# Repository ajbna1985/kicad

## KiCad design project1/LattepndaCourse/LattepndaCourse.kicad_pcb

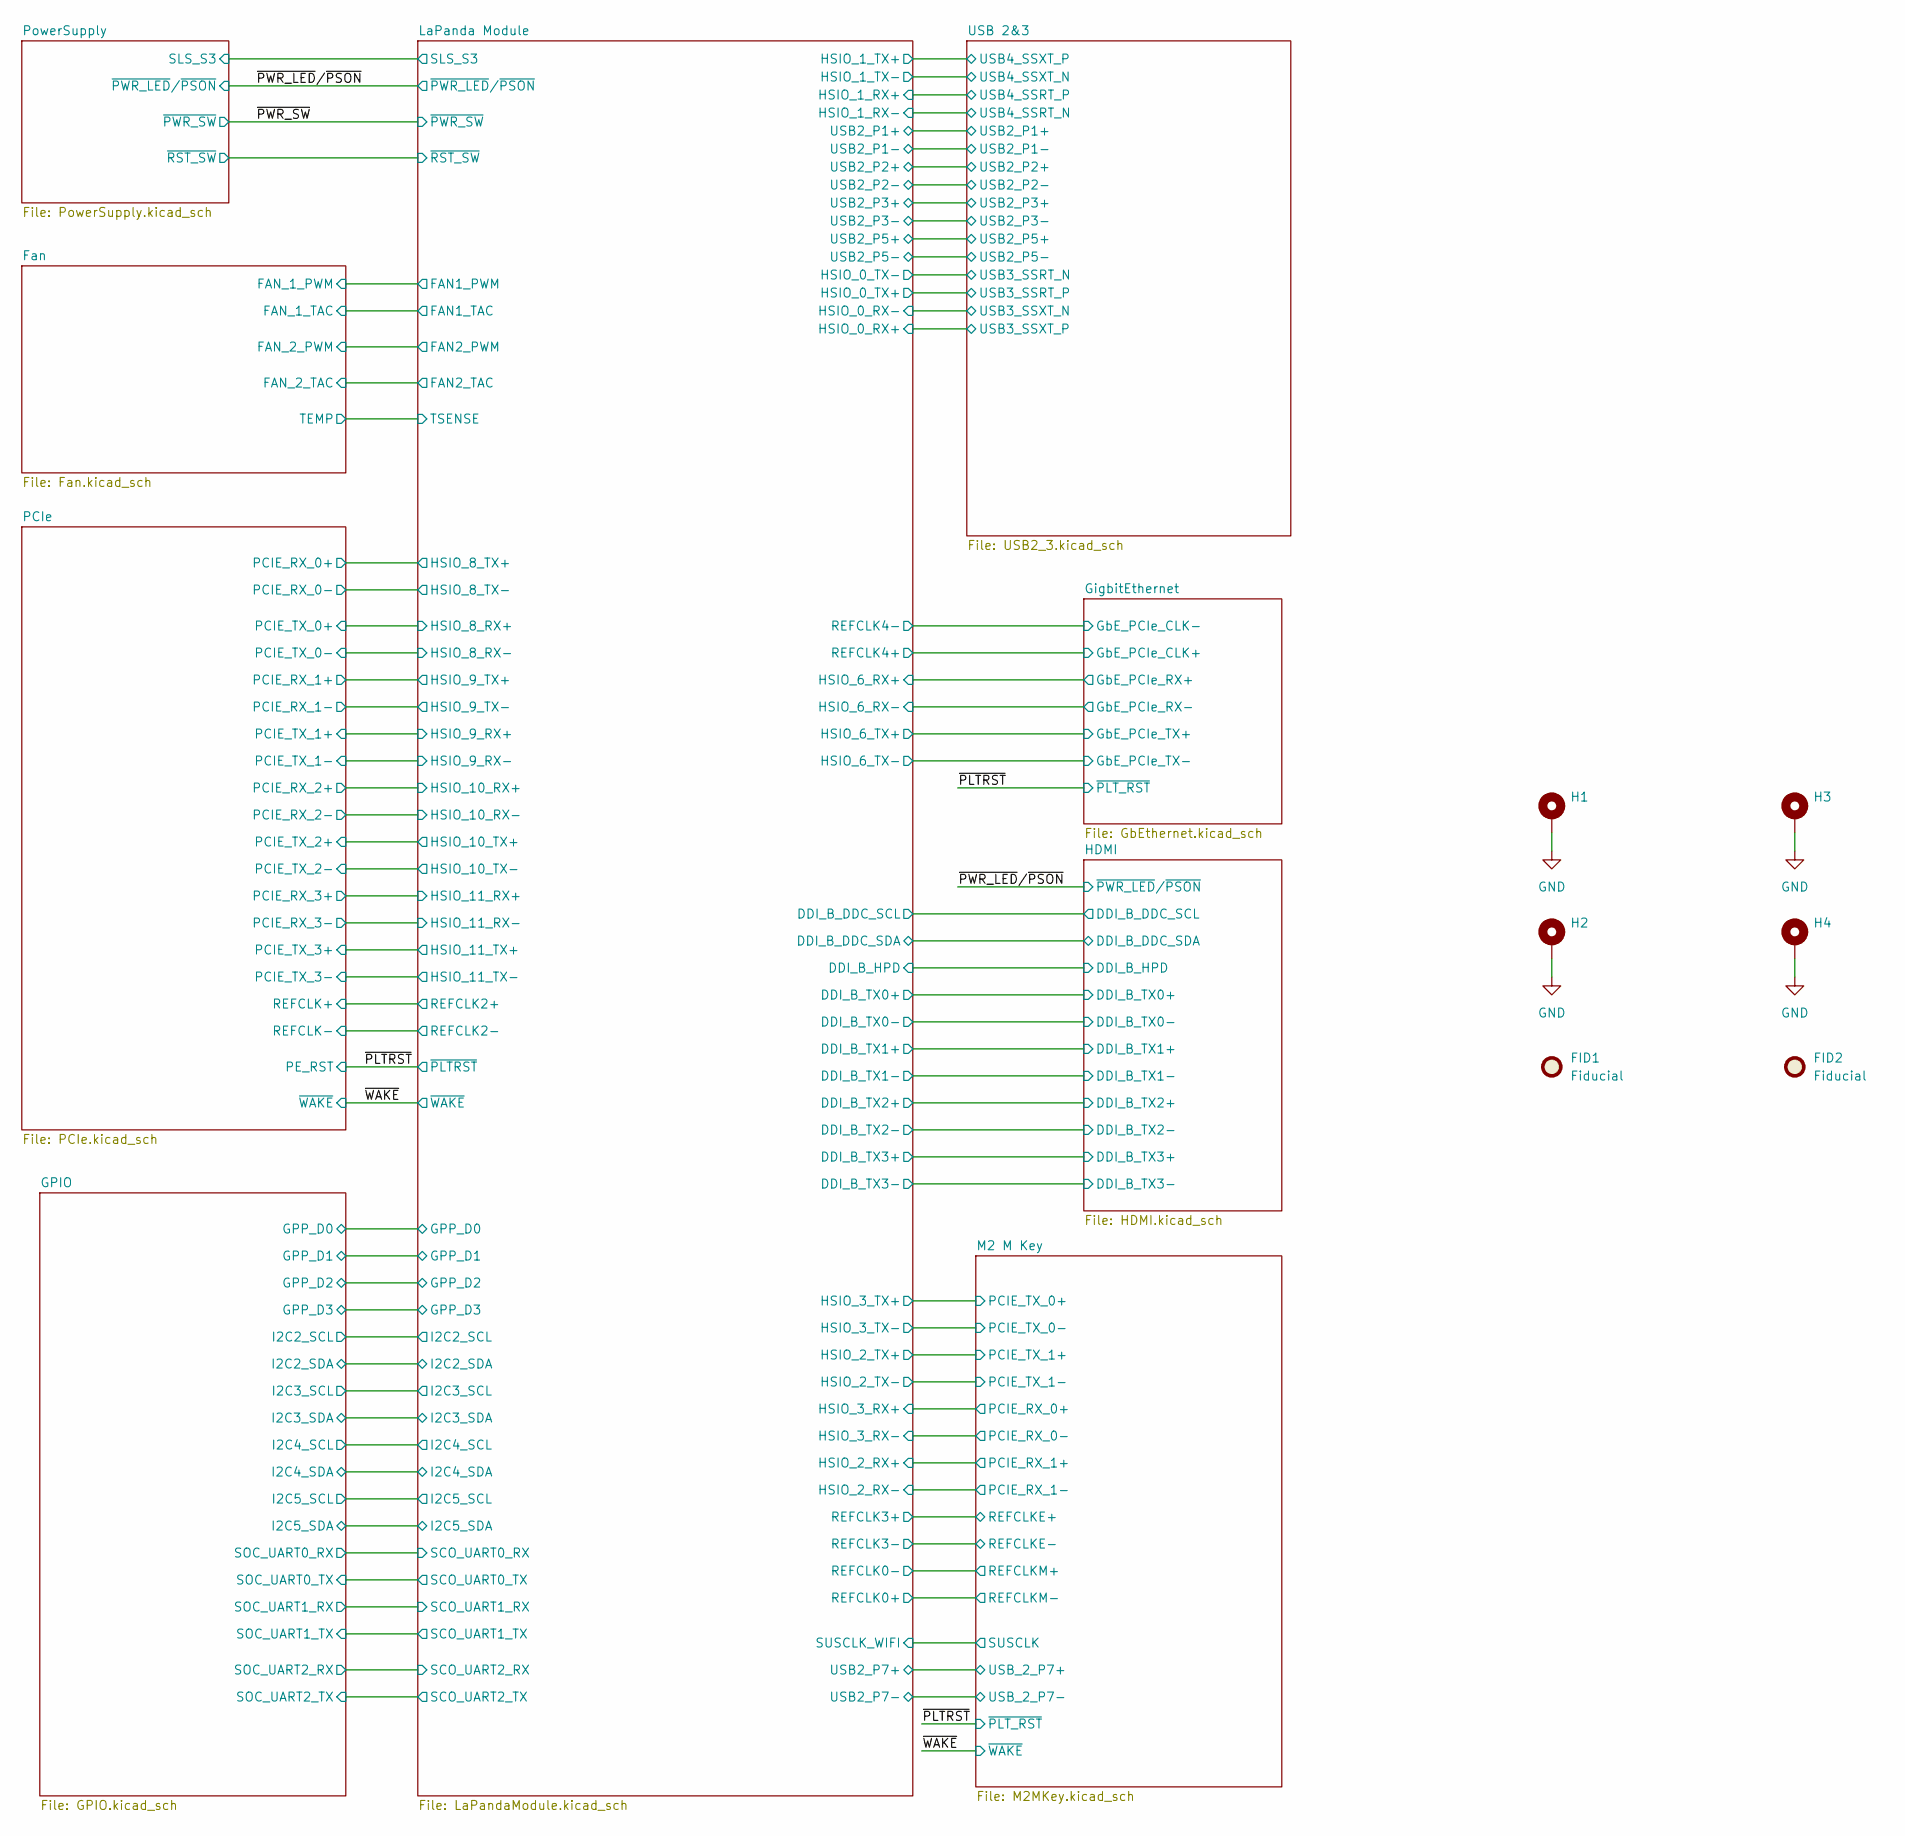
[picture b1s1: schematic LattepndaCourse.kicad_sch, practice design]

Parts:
FID1, FID2: Fiducial; Fiducial_0.5mm_Mask1mm
H1, H2, H3, H4: MountingHole_Pad; MountingHole_3.2mm_M3_Pad_Via

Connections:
+5V: H1.1 (1_1), H2.1 (1_1), H3.1 (1_1), H4.1 (1_1); also elsewhere on the board

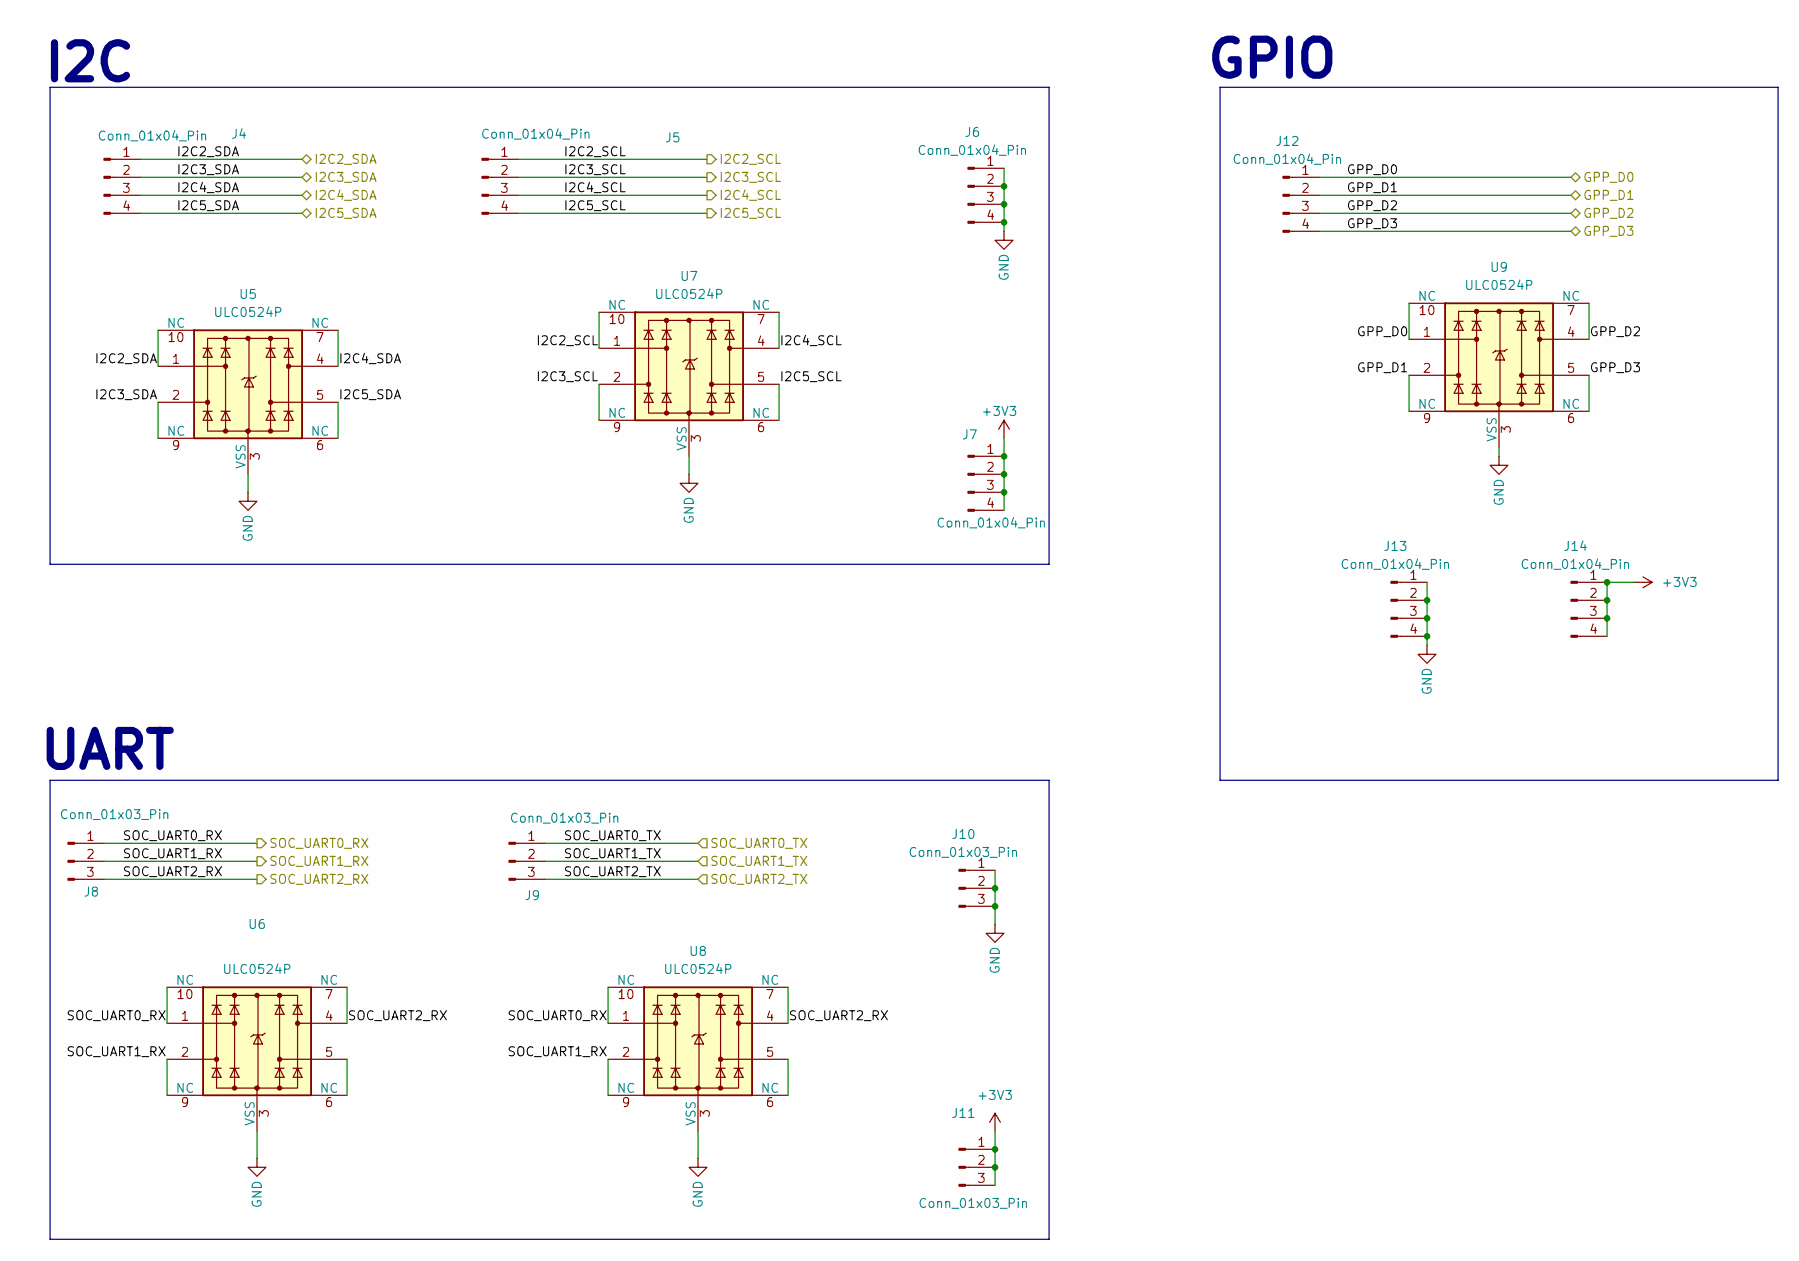
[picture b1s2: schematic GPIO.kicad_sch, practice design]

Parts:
J4, J5, J6, J7, J12, J13, J14: Conn_01x04_Pin; PinHeader_1x03_P2.54mm_Vertical
J8, J9, J10, J11: Conn_01x03_Pin; PinHeader_1x03_P2.54mm_Vertical
U5, U6, U7, U8, U9: ULC0524P; Diodes_UDFN-10_1.0x2.5mm_P0.5mm

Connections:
+3V3: J7.1, J7.2, J7.3, J7.4, J11.1, J11.2, J11.3, J14.1, J14.2, J14.3, J14.4; also elsewhere on the board
+5V: J6.1, J6.2, J6.3, J6.4, J10.1, J10.2, J10.3, J13.1, J13.2, J13.3, J13.4, U5.3 (VSS), U5.8 (VSS), U6.3 (VSS), U6.8 (VSS), U7.3 (VSS), U7.8 (VSS), U8.3 (VSS), U8.8 (VSS), U9.3 (VSS), U9.8 (VSS); also elsewhere on the board
/GPIO/GPP_D0: J12.1, U9.1, U9.10 (NC); also elsewhere on the board
/GPIO/GPP_D1: J12.2, U9.2, U9.9 (NC); also elsewhere on the board
/GPIO/GPP_D2: J12.3, U9.4, U9.7 (NC); also elsewhere on the board
/GPIO/GPP_D3: J12.4, U9.5, U9.6 (NC); also elsewhere on the board
/GPIO/I2C2_SCL: J5.1, U7.1, U7.10 (NC); also elsewhere on the board
/GPIO/I2C2_SDA: J4.1, U5.1, U5.10 (NC); also elsewhere on the board
/GPIO/I2C3_SCL: J5.2, U7.2, U7.9 (NC); also elsewhere on the board
/GPIO/I2C3_SDA: J4.2, U5.2, U5.9 (NC); also elsewhere on the board
/GPIO/I2C4_SCL: J5.3, U7.4, U7.7 (NC); also elsewhere on the board
/GPIO/I2C4_SDA: J4.3, U5.4, U5.7 (NC); also elsewhere on the board
/GPIO/I2C5_SCL: J5.4, U7.5, U7.6 (NC); also elsewhere on the board
/GPIO/I2C5_SDA: J4.4, U5.5, U5.6 (NC); also elsewhere on the board
/GPIO/SOC_UART0_RX: J8.1, U6.1, U6.10 (NC), U8.1, U8.10 (NC); also elsewhere on the board
/GPIO/SOC_UART0_TX: J9.1; also elsewhere on the board
/GPIO/SOC_UART1_RX: J8.2, U6.2, U6.9 (NC), U8.2, U8.9 (NC); also elsewhere on the board
/GPIO/SOC_UART1_TX: J9.2; also elsewhere on the board
/GPIO/SOC_UART2_RX: J8.3, U6.4, U6.7 (NC), U8.4, U8.7 (NC); also elsewhere on the board
/GPIO/SOC_UART2_TX: J9.3; also elsewhere on the board
unnamed: U6.5, U6.6 (NC)
unnamed: U8.5, U8.6 (NC)

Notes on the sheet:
UART
I2C
GPIO

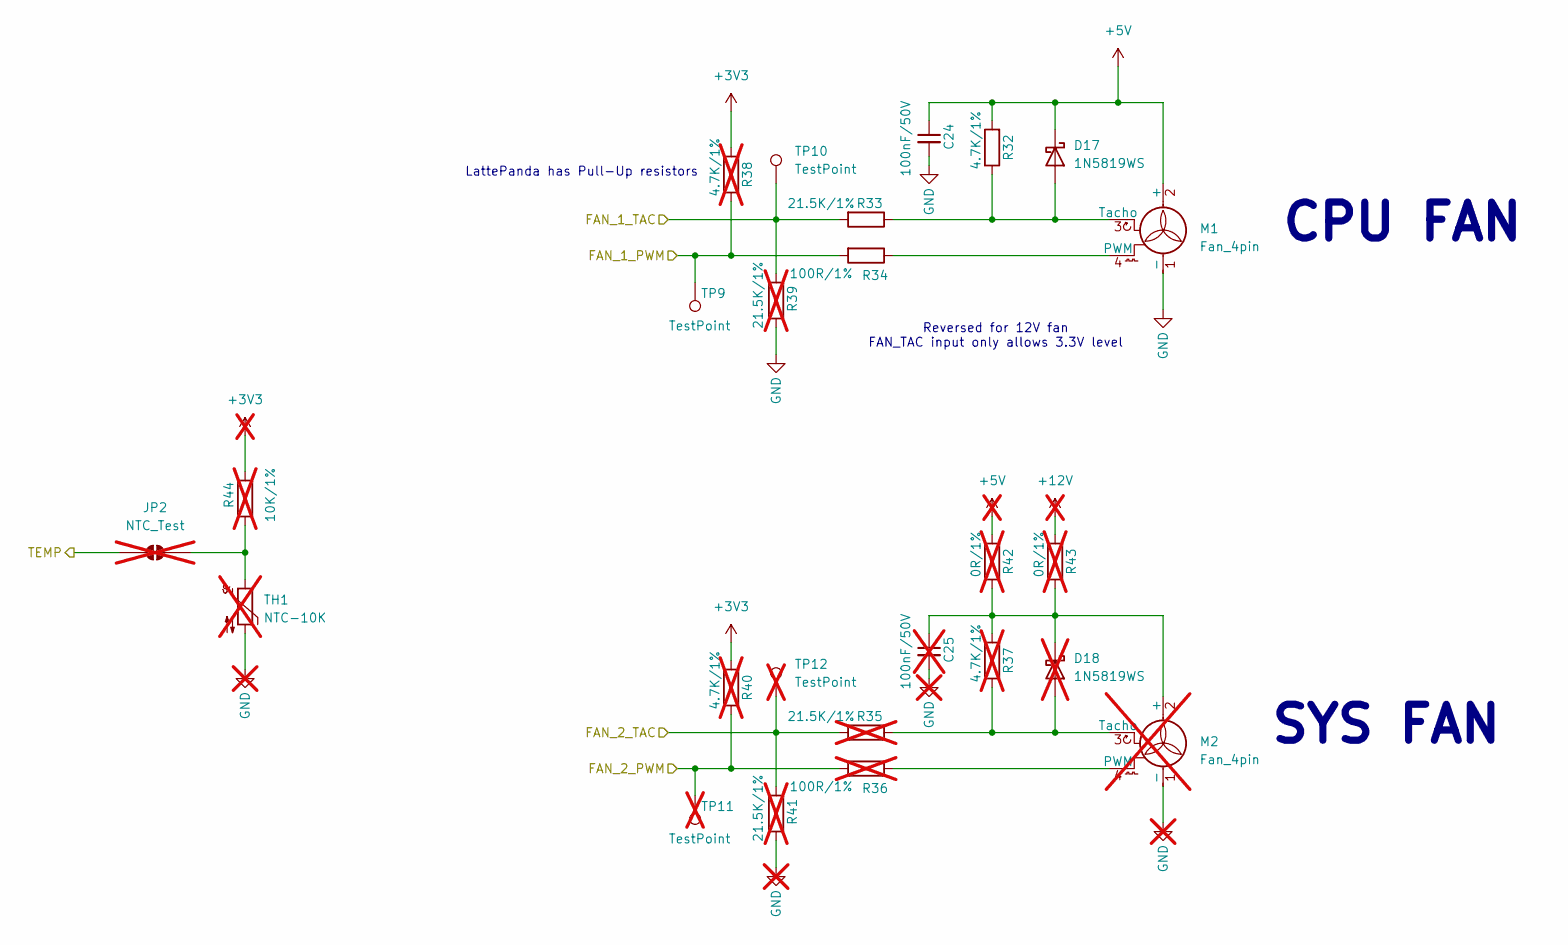
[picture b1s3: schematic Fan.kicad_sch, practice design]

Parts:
C24: 100nF/50V; C_0402_1005Metric
C25: 100nF/50V; C_0402_1005Metric; not fitted
D17: 1N5819WS; D_SOD-323
D18: 1N5819WS; D_SOD-323; not fitted
JP2: NTC_Test; SolderJumper-2_P1.3mm_Open_RoundedPad1.0x1.5mm; not fitted
M1: Fan_4pin; JST_PH_B4B-PH-K_1x04_P2.00mm_Vertical
M2: Fan_4pin; JST_PH_B4B-PH-K_1x04_P2.00mm_Vertical; not fitted
R32: 4.7K/1%; R_0402_1005Metric
R33: 21.5K/1%; R_0402_1005Metric
R34: 100R/1%; R_0402_1005Metric
R35, R39, R41: 21.5K/1%; R_0402_1005Metric; not fitted
R36: 100R/1%; R_0402_1005Metric; not fitted
R37, R38, R40: 4.7K/1%; R_0402_1005Metric; not fitted
R42, R43: 0R/1%; R_0402_1005Metric; not fitted
R44: 10K/1%; R_0402_1005Metric; not fitted
TH1: NTC-10K; R_0603_1608Metric; not fitted
TP9, TP10: TestPoint; TestPoint_Pad_D1.5mm
TP11, TP12: TestPoint; TestPoint_Pad_D1.5mm; not fitted

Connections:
+3V3: R38.2, R40.2, R44.1; also elsewhere on the board
+5V: C24.1, C24.2, C25.2, D17.1 (K), M1.1 (-), M1.2 (+), M2.1 (-), R32.2, R39.2, R41.2, R42.2, TH1.2; also elsewhere on the board
+12V: R43.2; also elsewhere on the board
/Fan/FAN_1_PWM: R34.2, R38.1, TP9.1 (1_1); also elsewhere on the board
/Fan/FAN_1_TAC: R33.2, R39.1, TP10.1 (1_1); also elsewhere on the board
/Fan/FAN_2_PWM: R36.2, R40.1, TP11.1 (1_1); also elsewhere on the board
/Fan/FAN_2_TAC: R35.2, R41.1, TP12.1 (1_1); also elsewhere on the board
/Fan/TEMP: JP2.1 (A); also elsewhere on the board
unnamed: D17.2 (A), M1.3 (Tacho), R32.1, R33.1
unnamed: D18.2 (A), M2.3 (Tacho), R35.1, R37.1
unnamed: C25.1, D18.1 (K), M2.2 (+), R37.2, R42.1, R43.1
unnamed: JP2.2 (B), R44.2, TH1.1
unnamed: M1.4 (PWM), R34.1
unnamed: M2.4 (PWM), R36.1

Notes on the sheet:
LattePanda has Pull-Up resistors
CPU FAN
SYS FAN
Reversed for 12V fan FAN_TAC input only allows 3.3V level

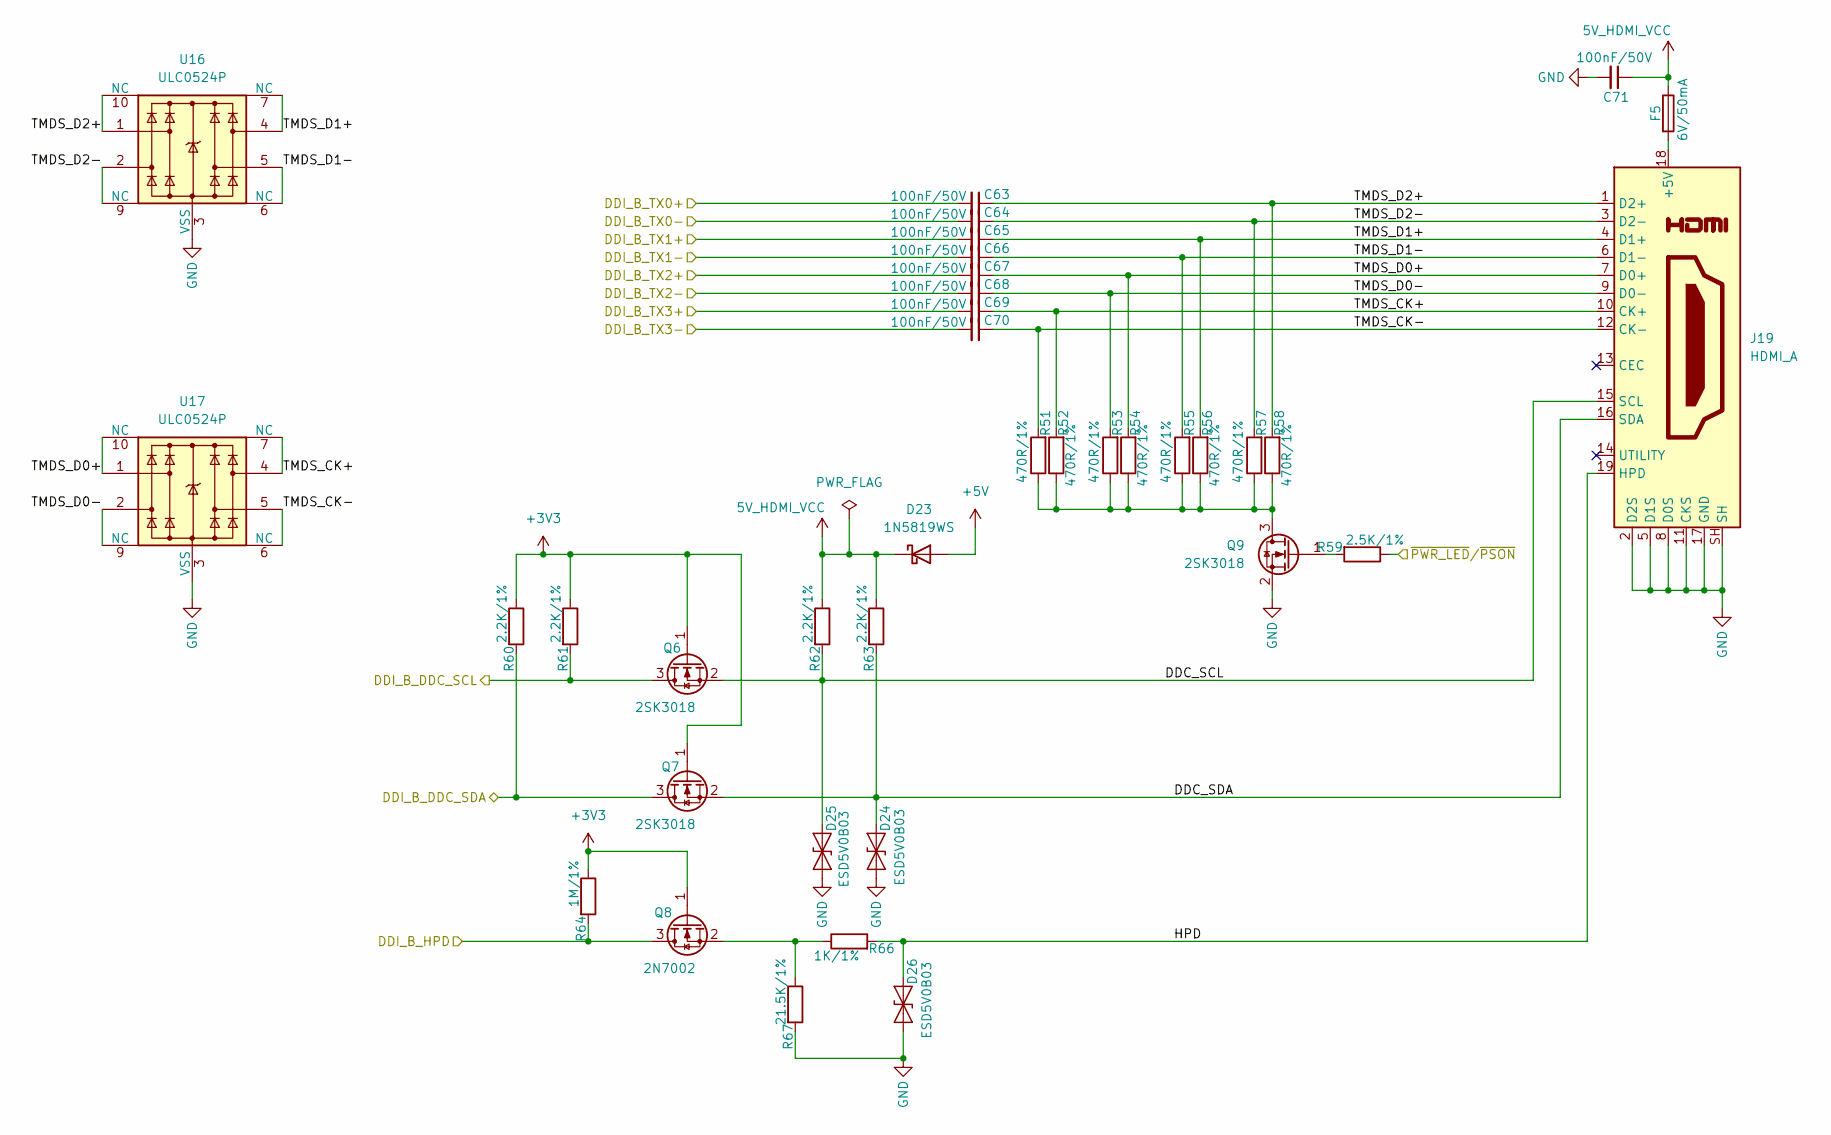
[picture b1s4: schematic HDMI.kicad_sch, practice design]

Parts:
C63, C64, C65, C66, C67, C68, C69, C70, C71: 100nF/50V; C_0603_1608Metric
D23: 1N5819WS; D_SOD-323
D24, D25, D26: ESD5V0B03; D_0402_1005Metric
F5: 6V/50mA; C_0603_1608Metric
J19: HDMI_A; HDMI_A_Molex_208658-1001_Horizontal
Q6, Q7, Q9: 2SK3018; SOT-23
Q8: 2N7002; SOT-23
R51, R52, R53, R54, R55, R56, R57, R58: 470R/1%; R_0402_1005Metric
R59: 2.5K/1%; R_0402_1005Metric
R60, R61, R62, R63: 2.2K/1%; R_0402_1005Metric
R64: 1M/1%; R_0402_1005Metric
R66: 1K/1%; R_0402_1005Metric
R67: 21.5K/1%; R_0402_1005Metric
U16, U17: ULC0524P; Diodes_UDFN-10_1.0x2.5mm_P0.5mm

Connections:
5V_HDMI_VCC: C71.1, D23.1 (K), F5.1, R62.1, R63.1
+3V3: Q6.1 (G), Q7.1 (G), Q8.1 (G), R60.1, R61.1, R64.1; also elsewhere on the board
+5V: C71.2, D23.2 (A), D24.1 (A1), D25.1 (A1), D26.1 (A1), J19.2 (D2S), J19.5 (D1S), J19.8 (D0S), J19.11 (CKS), J19.17 (GND), J19.SH, Q9.2 (S), R67.2, U16.3 (VSS), U16.8 (VSS), U17.3 (VSS), U17.8 (VSS); also elsewhere on the board
/HDMI/DDC_SCL: D25.2 (A2), J19.15 (SCL), Q6.2 (S), R62.2
/HDMI/DDC_SDA: D24.2 (A2), J19.16 (SDA), Q7.2 (S), R63.2
/HDMI/DDI_B_DDC_SCL: Q6.3 (D), R61.2; also elsewhere on the board
/HDMI/DDI_B_DDC_SDA: Q7.3 (D), R60.2; also elsewhere on the board
/HDMI/DDI_B_HPD: Q8.3 (D), R64.2; also elsewhere on the board
/HDMI/DDI_B_TX0+: C63.2; also elsewhere on the board
/HDMI/DDI_B_TX0-: C64.2; also elsewhere on the board
/HDMI/DDI_B_TX1+: C65.2; also elsewhere on the board
/HDMI/DDI_B_TX1-: C66.2; also elsewhere on the board
/HDMI/DDI_B_TX2+: C67.2; also elsewhere on the board
/HDMI/DDI_B_TX2-: C68.2; also elsewhere on the board
/HDMI/DDI_B_TX3+: C69.2; also elsewhere on the board
/HDMI/DDI_B_TX3-: C70.2; also elsewhere on the board
/HDMI/HPD: D26.2 (A2), J19.19 (HPD), R66.2
/HDMI/TMDS_CK+: C69.1, J19.10 (CK+), R52.2, U17.4, U17.7 (NC)
/HDMI/TMDS_CK-: C70.1, J19.12 (CK-), R51.2, U17.5, U17.6 (NC)
/HDMI/TMDS_D0+: C67.1, J19.7 (D0+), R54.2, U17.1, U17.10 (NC)
/HDMI/TMDS_D0-: C68.1, J19.9 (D0-), R53.2, U17.2, U17.9 (NC)
/HDMI/TMDS_D1+: C65.1, J19.4 (D1+), R56.2, U16.4, U16.7 (NC)
/HDMI/TMDS_D1-: C66.1, J19.6 (D1-), R55.2, U16.5, U16.6 (NC)
/HDMI/TMDS_D2+: C63.1, J19.1 (D2+), R58.2, U16.1, U16.10 (NC)
/HDMI/TMDS_D2-: C64.1, J19.3 (D2-), R57.2, U16.2, U16.9 (NC)
/~PWR_LED/~PSON: R59.1; also elsewhere on the board
unnamed: F5.2, J19.18 (+5V)
unnamed: Q8.2 (S), R66.1, R67.1
unnamed: Q9.3 (D), R51.1, R52.1, R53.1, R54.1, R55.1, R56.1, R57.1, R58.1
unnamed: Q9.1 (G), R59.2

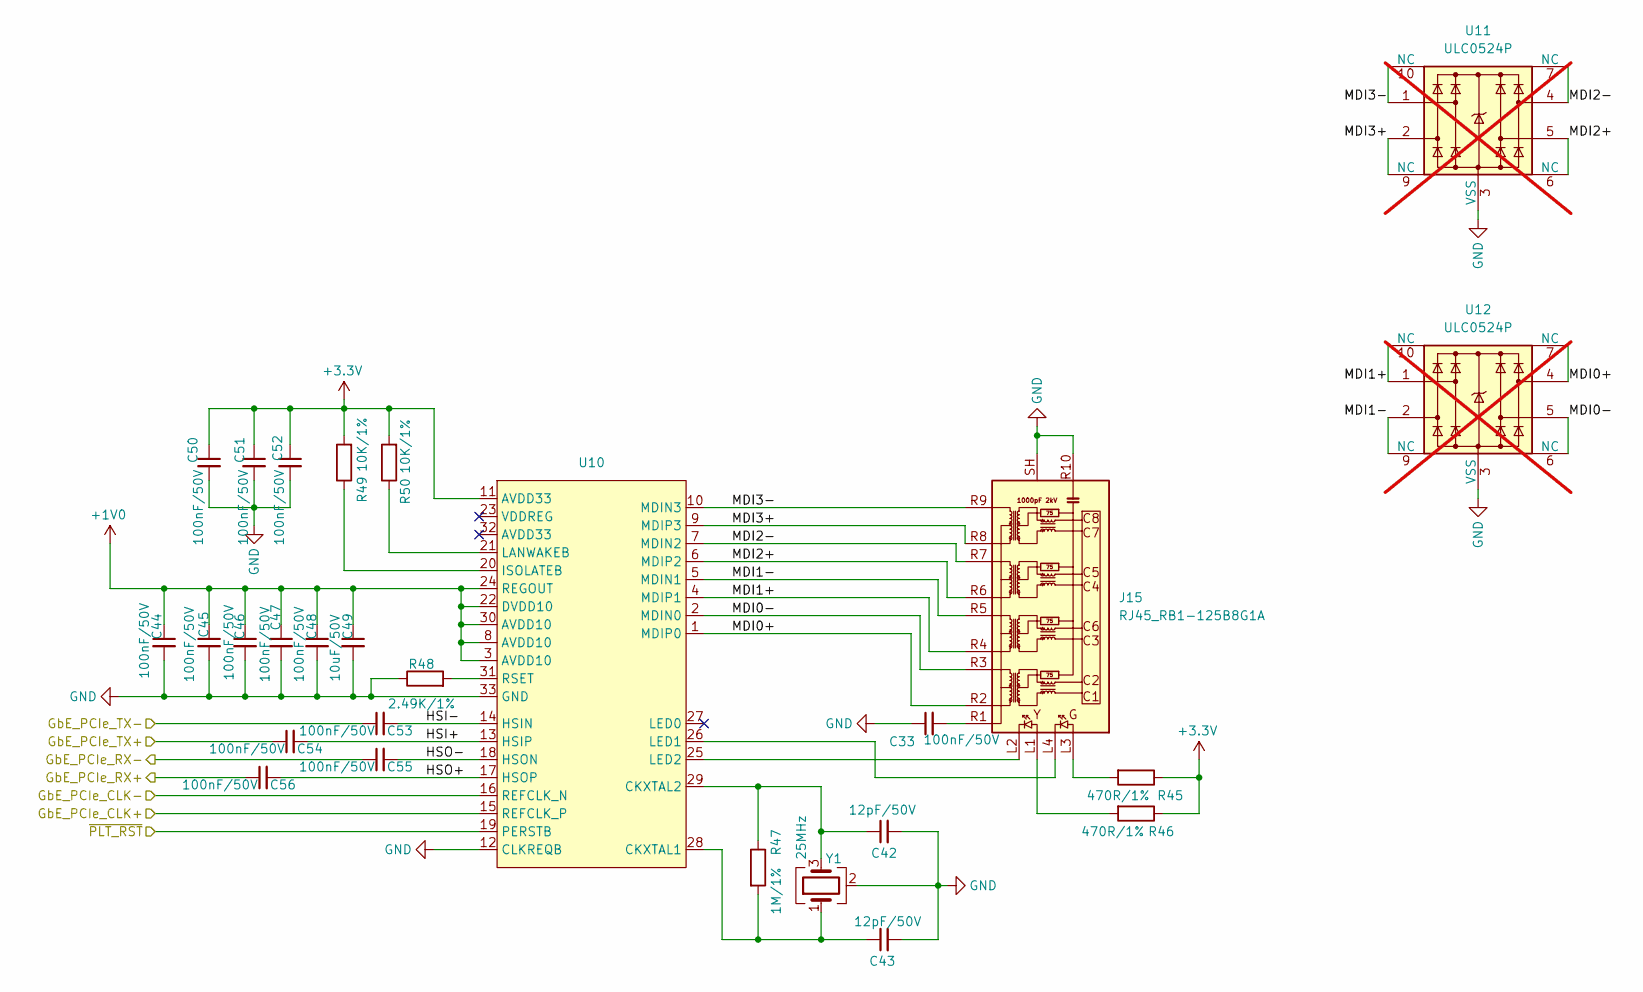
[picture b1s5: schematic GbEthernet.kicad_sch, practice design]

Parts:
C33, C44, C45, C46, C47, C48, C50, C51, C52, C53, C54, C55, C56: 100nF/50V; C_0402_1005Metric
C42, C43: 12pF/50V; C_0402_1005Metric
C49: 10uF/50V; C_0402_1005Metric
J15: RJ45_RB1-125B8G1A; RJ45_UDE_RB1-125B8G1A
R45, R46: 470R/1%; R_0402_1005Metric
R47: 1M/1%; R_0402_1005Metric
R48: 2.49K/1%; R_0603_1608Metric
R49, R50: 10K/1%; R_0402_1005Metric
U10: RTL8111H-CG-RH; QFN-32-1EP_4x4mm_P0.4mm_EP2.65x2.65mm
U11, U12: ULC0524P; Diodes_UDFN-10_1.0x2.5mm_P0.5mm; not fitted
Y1: 25MHz; Crystal_SMD_3225-4Pin_3.2x2.5mm

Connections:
+1V0: C44.1, C45.1, C46.1, C47.1, C48.1, C49.1, U10.3 (AVDD10), U10.8 (AVDD10), U10.22 (DVDD10), U10.24 (REGOUT), U10.30 (AVDD10)
+3.3V: C50.1, C51.1, C52.1, R45.1, R46.1, R49.2, R50.2, U10.11 (AVDD33); also elsewhere on the board
+5V: C33.1, C42.2, C43.2, C44.2, C45.2, C46.2, C47.2, C48.2, C49.2, C50.2, C51.2, C52.2, J15.R10 (GND), J15.SH, R48.1, U10.12 (CLKREQB), U10.33 (GND), U11.3 (VSS), U11.8 (VSS), U12.3 (VSS), U12.8 (VSS), Y1.2 (G), Y1.4 (G); also elsewhere on the board
/GigbitEthernet/GbE_PCIe_CLK+: U10.15 (REFCLK_P); also elsewhere on the board
/GigbitEthernet/GbE_PCIe_CLK-: U10.16 (REFCLK_N); also elsewhere on the board
/GigbitEthernet/GbE_PCIe_RX+: C56.1; also elsewhere on the board
/GigbitEthernet/GbE_PCIe_RX-: C55.1; also elsewhere on the board
/GigbitEthernet/GbE_PCIe_TX+: C54.1; also elsewhere on the board
/GigbitEthernet/GbE_PCIe_TX-: C53.1; also elsewhere on the board
/GigbitEthernet/HSI+: C54.2, U10.13 (HSIP)
/GigbitEthernet/HSI-: C53.2, U10.14 (HSIN)
/GigbitEthernet/HSO+: C56.2, U10.17 (HSOP)
/GigbitEthernet/HSO-: C55.2, U10.18 (HSON)
/GigbitEthernet/MDI0+: J15.R2 (TD1+), U10.1 (MDIP0), U12.4, U12.7 (NC)
/GigbitEthernet/MDI0-: J15.R3 (TD1-), U10.2 (MDIN0), U12.5, U12.6 (NC)
/GigbitEthernet/MDI1+: J15.R4 (TD2+), U10.4 (MDIP1), U12.1, U12.10 (NC)
/GigbitEthernet/MDI1-: J15.R5 (TD2-), U10.5 (MDIN1), U12.2, U12.9 (NC)
/GigbitEthernet/MDI2+: J15.R6 (TD3+), U10.6 (MDIP2), U11.5, U11.6 (NC)
/GigbitEthernet/MDI2-: J15.R7 (TD3-), U10.7 (MDIN2), U11.4, U11.7 (NC)
/GigbitEthernet/MDI3+: J15.R8 (TD4+), U10.9 (MDIP3), U11.2, U11.9 (NC)
/GigbitEthernet/MDI3-: J15.R9 (TD4-), U10.10 (MDIN3), U11.1, U11.10 (NC)
/~PLTRST: U10.19 (PERSTB); also elsewhere on the board
unnamed: C33.2, J15.R1 (CT)
unnamed: J15.L1, R46.2
unnamed: J15.L3, R45.2
unnamed: C43.1, R47.2, U10.28 (CKXTAL1), Y1.1
unnamed: C42.1, R47.1, U10.29 (CKXTAL2), Y1.3
unnamed: R49.1, U10.20 (ISOLATEB)
unnamed: R50.1, U10.21 (LANWAKEB)
unnamed: J15.L4, U10.26 (LED1)
unnamed: J15.L2, U10.25 (LED2)
unnamed: R48.2, U10.31 (RSET)

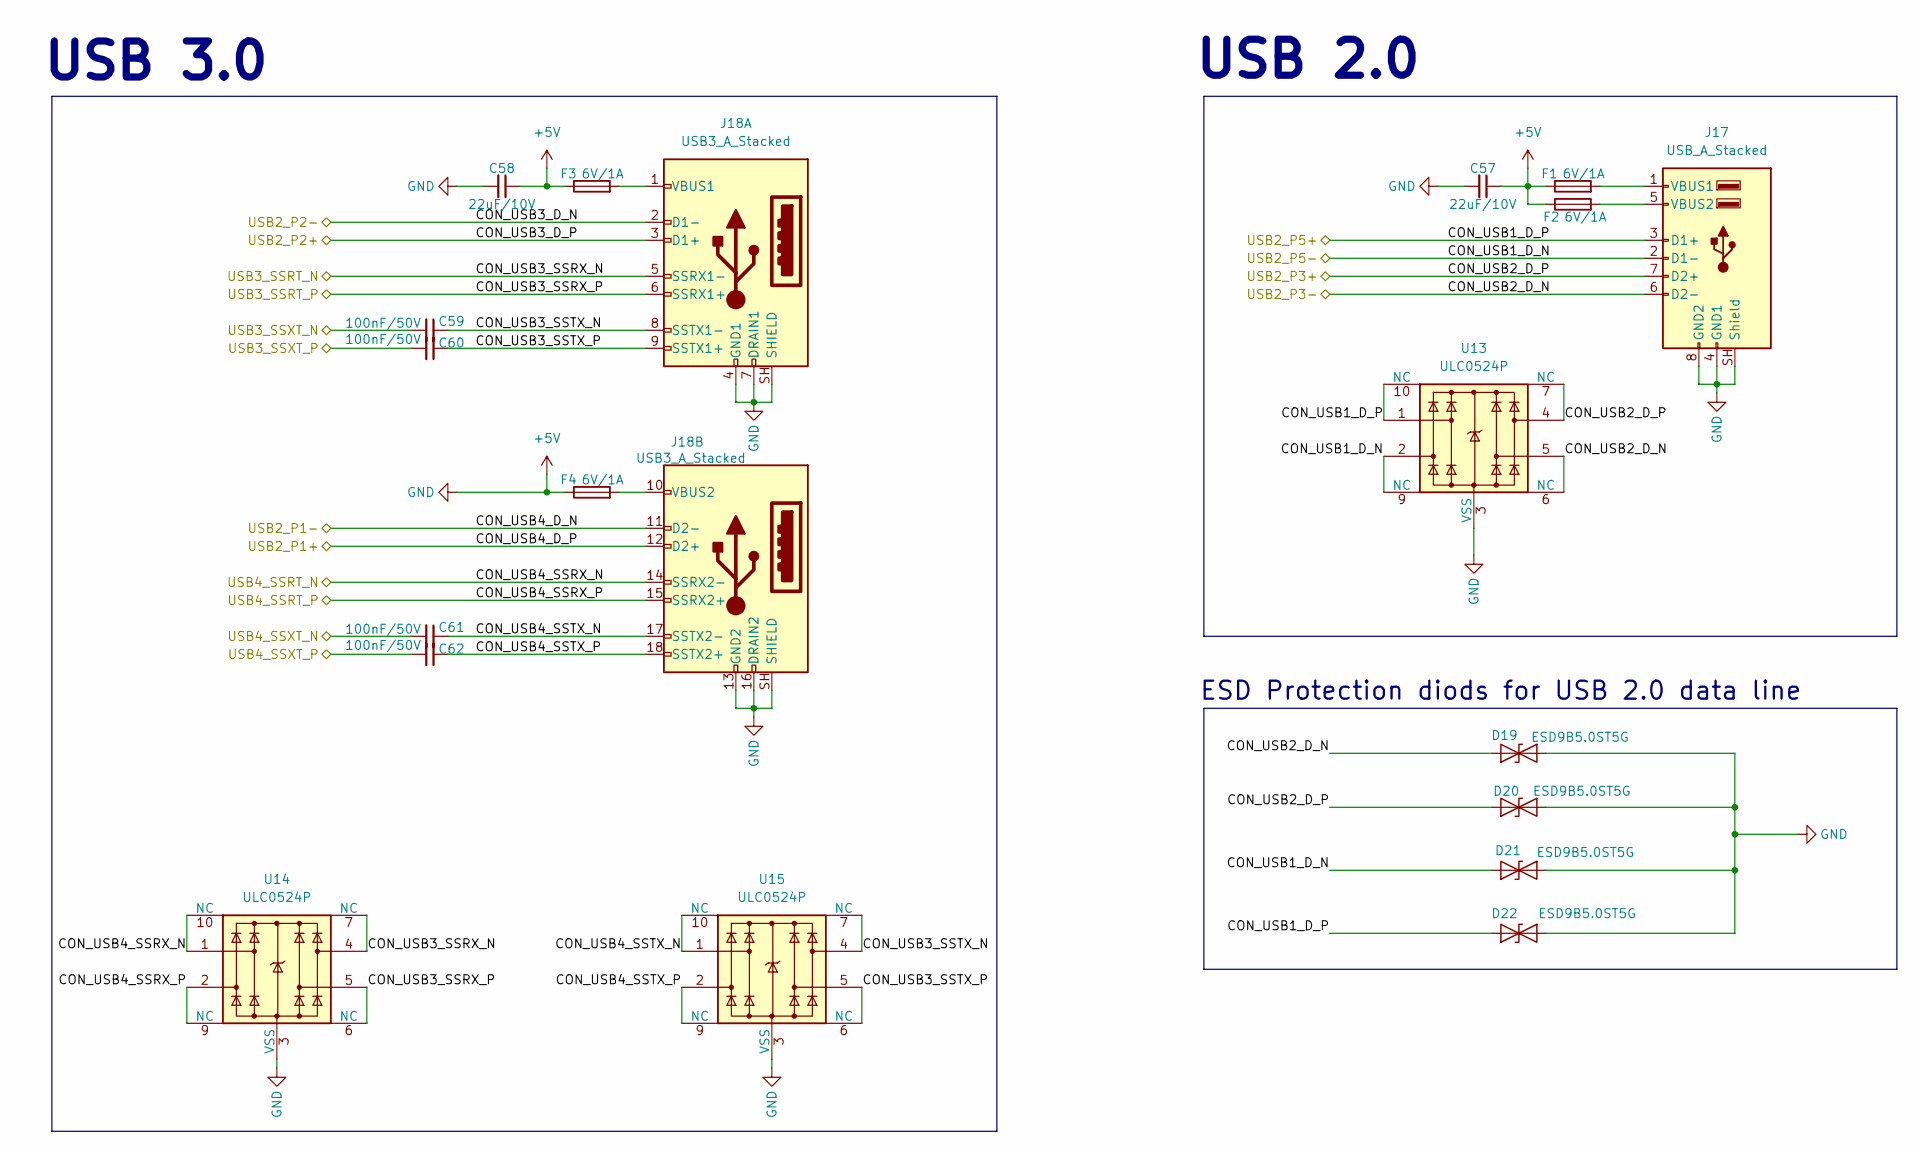
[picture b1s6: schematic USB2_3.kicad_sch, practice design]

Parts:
C57, C58: 22uF/10V; C_0603_1608Metric
C59, C60, C61, C62: 100nF/50V; C_0603_1608Metric
D19, D20, D21, D22: ESD9B5.0ST5G; D_0402_1005Metric
F1, F2, F3, F4: 6V/1A; Fuse_0805_2012Metric
J17: USB_A_Stacked; USB_A_CUI_UJ2-ADH-TH_Horizontal_Stacked
J18: USB3_A_Stacked; USB3_A_Molex_48406-0001_Horizontal_Stacked
U13, U14, U15: ULC0524P; Diodes_UDFN-10_1.0x2.5mm_P0.5mm

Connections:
+5V: C57.1, C57.2, C58.1, C58.2, D19.2 (A2), D20.2 (A2), D21.2 (A2), D22.2 (A2), F1.1, F2.1, F3.1, F4.1, J17.4 (GND1), J17.8 (GND2), J17.SH (Shield), J18.4 (GND1), J18.7 (DRAIN1), J18.13 (GND2), J18.16 (DRAIN2), J18.SH (SHIELD), U13.3 (VSS), U13.8 (VSS), U14.3 (VSS), U14.8 (VSS), U15.3 (VSS), U15.8 (VSS); also elsewhere on the board
/LaPanda Module/HSIO_0_RX+: C60.2; also elsewhere on the board
/LaPanda Module/HSIO_0_RX-: C59.2; also elsewhere on the board
/LaPanda Module/HSIO_1_TX+: C62.2; also elsewhere on the board
/LaPanda Module/HSIO_1_TX-: C61.2; also elsewhere on the board
/USB 2&3/CON_USB1_D_N: D21.1 (A1), J17.2 (D1-), U13.2, U13.9 (NC); also elsewhere on the board
/USB 2&3/CON_USB1_D_P: D22.1 (A1), J17.3 (D1+), U13.1, U13.10 (NC); also elsewhere on the board
/USB 2&3/CON_USB2_D_N: D19.1 (A1), J17.6 (D2-), U13.5, U13.6 (NC); also elsewhere on the board
/USB 2&3/CON_USB2_D_P: D20.1 (A1), J17.7 (D2+), U13.4, U13.7 (NC); also elsewhere on the board
/USB 2&3/CON_USB3_D_N: J18.2 (D1-); also elsewhere on the board
/USB 2&3/CON_USB3_D_P: J18.3 (D1+); also elsewhere on the board
/USB 2&3/CON_USB3_SSRX_N: J18.5 (SSRX1-), U14.4, U14.7 (NC); also elsewhere on the board
/USB 2&3/CON_USB3_SSRX_P: J18.6 (SSRX1+), U14.5, U14.6 (NC); also elsewhere on the board
/USB 2&3/CON_USB3_SSTX_N: C59.1, J18.8 (SSTX1-), U15.4, U15.7 (NC)
/USB 2&3/CON_USB3_SSTX_P: C60.1, J18.9 (SSTX1+), U15.5, U15.6 (NC)
/USB 2&3/CON_USB4_D_N: J18.11 (D2-); also elsewhere on the board
/USB 2&3/CON_USB4_D_P: J18.12 (D2+); also elsewhere on the board
/USB 2&3/CON_USB4_SSRX_N: J18.14 (SSRX2-), U14.1, U14.10 (NC); also elsewhere on the board
/USB 2&3/CON_USB4_SSRX_P: J18.15 (SSRX2+), U14.2, U14.9 (NC); also elsewhere on the board
/USB 2&3/CON_USB4_SSTX_N: C61.1, J18.17 (SSTX2-), U15.1, U15.10 (NC)
/USB 2&3/CON_USB4_SSTX_P: C62.1, J18.18 (SSTX2+), U15.2, U15.9 (NC)
unnamed: F1.2, J17.1 (VBUS1)
unnamed: F2.2, J17.5 (VBUS2)
unnamed: F3.2, J18.1 (VBUS1)
unnamed: F4.2, J18.10 (VBUS2)

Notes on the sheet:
USB 2.0
USB 3.0
ESD Protection diods for USB 2.0 data line
